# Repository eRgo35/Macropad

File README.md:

# Macropad

My first PCB Schematic. A useful multipurpose Macropad.

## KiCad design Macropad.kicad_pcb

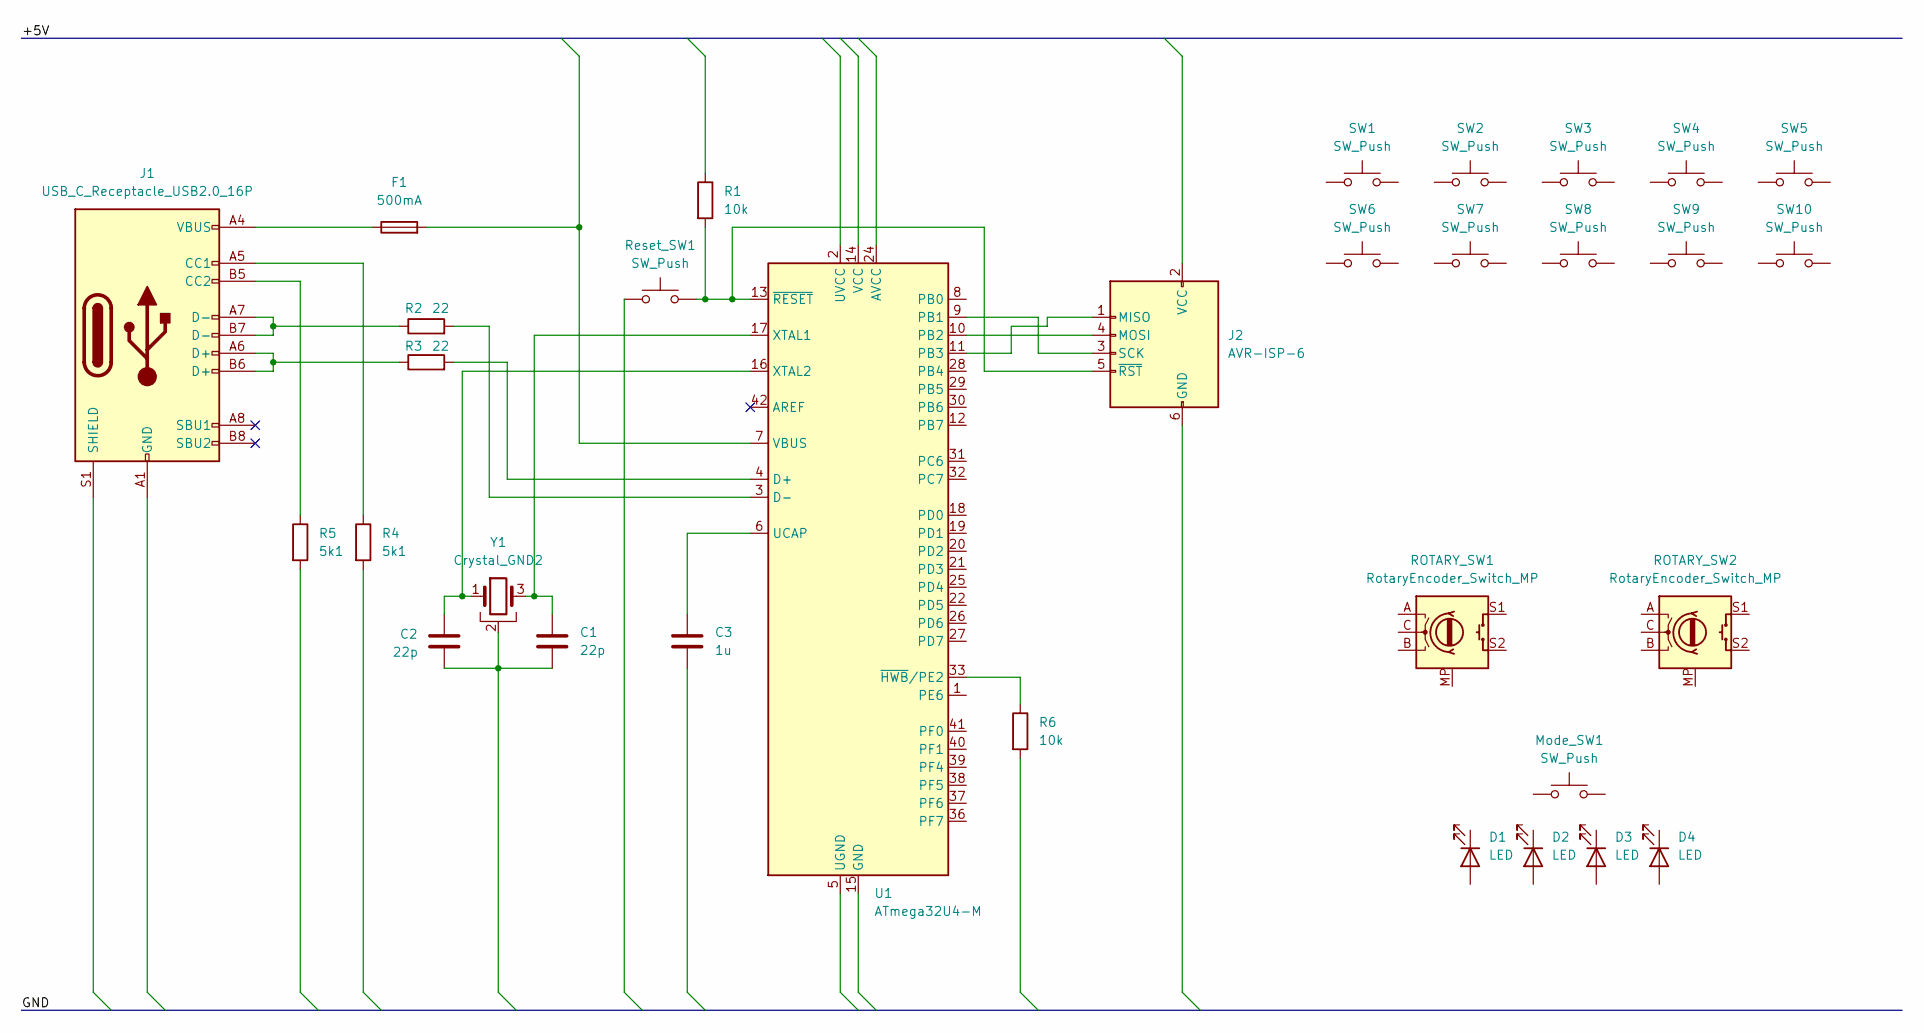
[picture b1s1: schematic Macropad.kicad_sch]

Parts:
C1, C2: 22p; C_0201_0603Metric_Pad0.64x0.40mm_HandSolder
C3: 1u; C_0201_0603Metric_Pad0.64x0.40mm_HandSolder
D1, D2, D3, D4: LED; LED_D1.8mm_W3.3mm_H2.4mm
F1: 500mA; Fuse_0603_1608Metric
J1: USB_C_Receptacle_USB2.0_16P; USB_C_Receptacle_GCT_USB4105-xx-A_16P_TopMnt_Horizontal
J2: AVR-ISP-6; IDC-Header_2x03_P2.54mm_Vertical_SMD
Mode_SW1: SW_Push; SW_PUSH-12mm
R1, R6: 10k; R_Axial_DIN0204_L3.6mm_D1.6mm_P5.08mm_Horizontal
R2, R3: 22; R_Axial_DIN0204_L3.6mm_D1.6mm_P5.08mm_Horizontal
R4, R5: 5k1; R_Axial_DIN0204_L3.6mm_D1.6mm_P5.08mm_Horizontal
ROTARY_SW1, ROTARY_SW2: RotaryEncoder_Switch_MP; RotaryEncoder_Alps_EC12E-Switch_Vertical_H20mm
Reset_SW1: SW_Push; SW_PUSH_6mm
SW1, SW2, SW3, SW4, SW5, SW6, SW7, SW8, SW9, SW10: SW_Push; SW_Cherry_MX_PCB
U1: ATmega32U4-M; QFN-44-1EP_7x7mm_P0.5mm_EP5.2x5.2mm
Y1: Crystal_GND2; Resonator-3Pin_W7.0mm_H2.5mm

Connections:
unnamed: C1.2, C2.2, Y1.2
unnamed: F1.1, J1.A4 (VBUS), J1.A9 (VBUS), J1.B4 (VBUS), J1.B9 (VBUS)
unnamed: J1.A5 (CC1), R4.1
unnamed: J1.B5 (CC2), R5.1
unnamed: J1.A6 (D+), J1.B6 (D+), R3.1
unnamed: J1.A7 (D-), J1.B7 (D-), R2.1
unnamed: J1.A1 (GND), J1.A12 (GND), J1.B1 (GND), J1.B12 (GND)
unnamed: J2.1 (MISO), U1.11 (PB3)
unnamed: J2.4 (MOSI), U1.10 (PB2)
unnamed: J2.3 (SCK), U1.9 (PB1)
unnamed: J2.5 (~RST), R1.2, Reset_SW1.2, U1.13 (~RESET)
unnamed: U1.24 (AVCC), U1.44 (AVCC)
unnamed: R3.2, U1.4 (D+)
unnamed: R2.2, U1.3 (D-)
unnamed: U1.15 (GND), U1.23 (GND), U1.35 (GND), U1.43 (GND), U1.45 (GND)
unnamed: C3.1, U1.6 (UCAP)
unnamed: F1.2, U1.7 (VBUS)
unnamed: U1.14 (VCC), U1.34 (VCC)
unnamed: C1.1, U1.17 (XTAL1), Y1.3
unnamed: C2.1, U1.16 (XTAL2), Y1.1
unnamed: R6.1, U1.33 (~HWB/PE2)

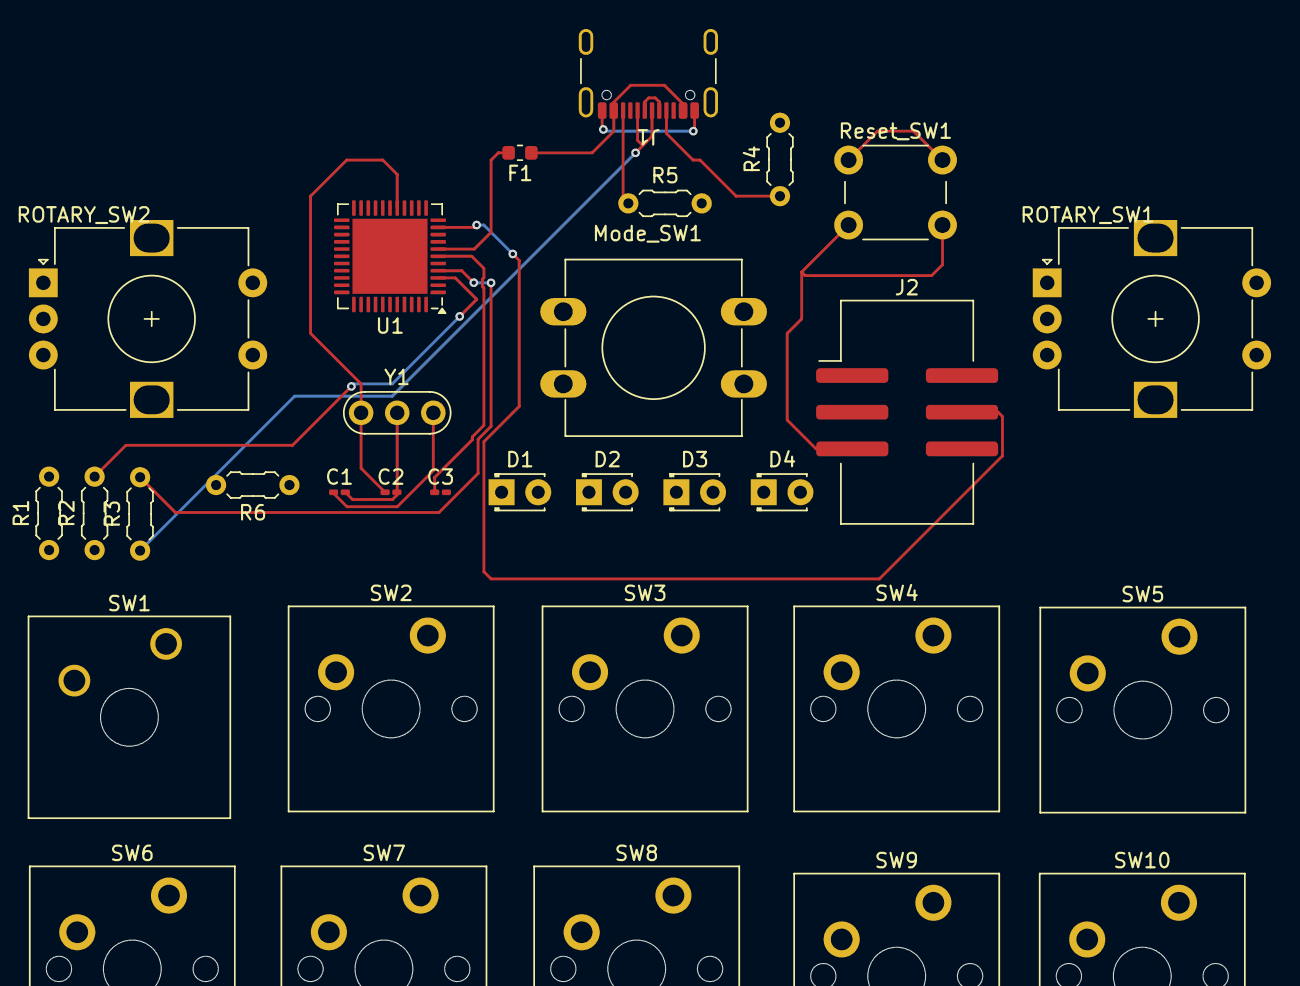
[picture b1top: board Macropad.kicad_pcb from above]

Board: 2 copper layers, 32 parts (0 on the bottom side), 21 nets.

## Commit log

2024-06-21 Schematic Init
2024-06-22 component layout
2024-06-28 futher backups sync
